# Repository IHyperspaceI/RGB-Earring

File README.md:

An earring with 10 RGB LEDs powered by a 12mm coin cell. An ATTiny1616 MCU controls the LEDs in rows, so PWM control and patterns can be made.

The tab on the bottom is to get the battery holder assembled by JLCPCB, which then will be manually desoldered and soldered to the back of the earring. The tab on the bottom can then be cut off. 

The Keystone 3000 can be ordered from other sources, however shipping is egregiously expensive from Mouser, Digikey, etc., and double sided PCBA also adds cost. Implementing a cutaway tab allows single-side PCBA and takes advantage of JLC's stock so costs associated with double-sided PCBA can be circumvented and shipping costs only need to be paid for one item.

Top Layer:

Bottom Layer

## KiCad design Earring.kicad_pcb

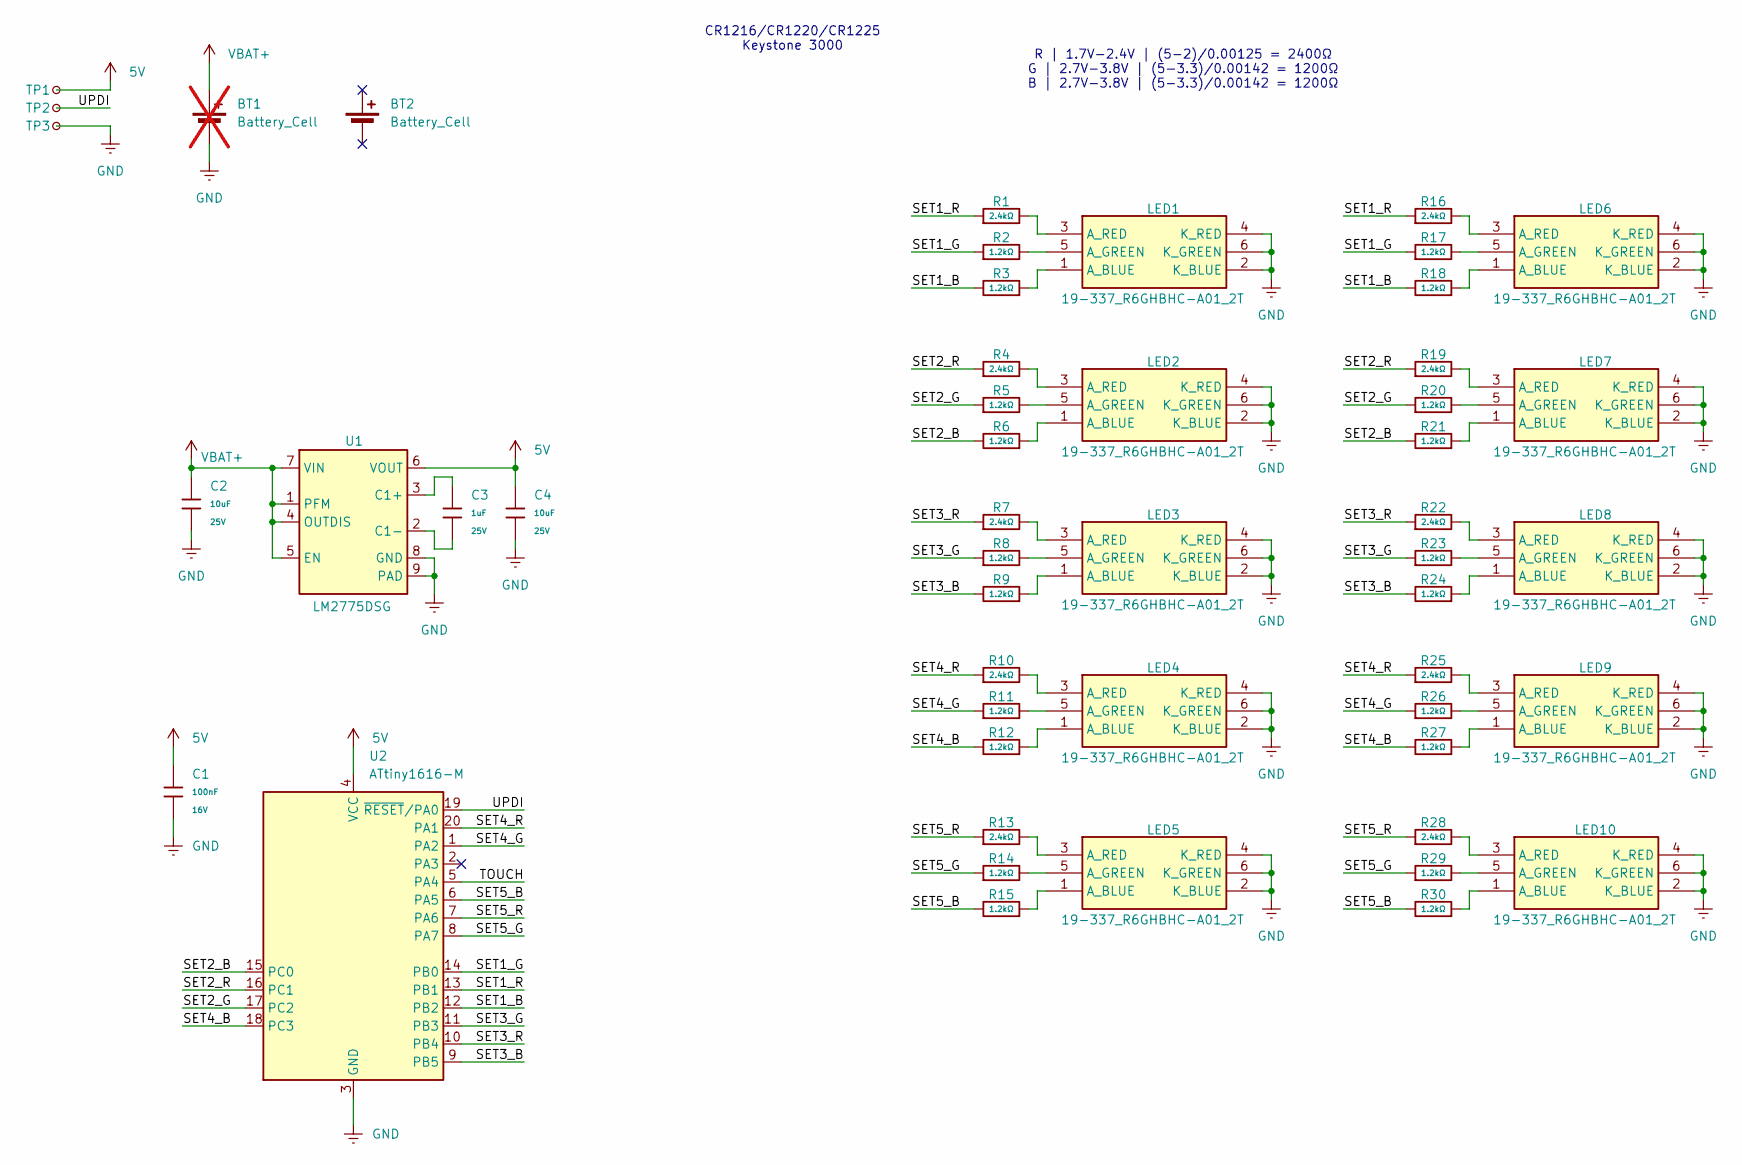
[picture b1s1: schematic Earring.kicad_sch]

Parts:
BT1: Battery_Cell; BatteryHolder_Keystone_3000_1x12mm; not fitted
BT2: Battery_Cell; BatteryHolder_Keystone_3000_1x12mm
C1: 100nF; C_0402; Voltage Rated 16V; Tolerance ±10%; Part CL05B104KO5NNNC; LCSC C1525
C2, C4: 10uF; C_0603; Voltage Rated 25V; Tolerance ±20%; Part CL10A106MA8NRNC; LCSC C96446
C3: 1uF; C_0402; Voltage Rated 25V; Tolerance ±10%; Part CL05A105KA5NQNC; LCSC C52923
LED1, LED2, LED3, LED4, LED5, LED6, LED7, LED8, LED9, LED10: 19-337_R6GHBHC-A01_2T; Mouser Part Number 638-19337R6GHBHCA01T
R1, R4, R7, R10, R13, R16, R19, R22, R25, R28: 2.4kΩ; R_0402; Overload Voltage (Max) 50V; Tolerance ±1%; Part 0402WGF2401TCE; LCSC C25882
R2, R3, R5, R6, R8, R9, R11, R12, R14, R15, R17, R18, R20, R21, R23, R24, R26, R27, R29, R30: 1.2kΩ; R_0402; Overload Voltage (Max) 50V; Tolerance ±1%; Part 0402WGF1201TCE; LCSC C25862
TP1, TP2: TestPoint_Small; TestPoint_Pad_D1.5mm
TP3: TestPoint_Small; TestPoint_Loop_D2.60mm_Drill0.9mm_Beaded
U1: LM2775DSG; WSON-8-1EP_2x2mm_P0.5mm_EP0.9x1.6mm_ThermalVias
U2: ATtiny1616-M; VQFN-20-1EP_3x3mm_P0.4mm_EP1.7x1.7mm

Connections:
5V: C1.1, C4.1, TP1.1 (1_1), U1.6 (VOUT), U2.4 (VCC)
/SET1_B: R3.2, R18.2, U2.12 (PB2)
/SET1_G: R2.1, R17.1, U2.14 (PB0)
/SET1_R: R1.1, R16.1, U2.13 (PB1)
/SET2_B: R6.2, R21.2, U2.15 (PC0)
/SET2_G: R5.1, R20.1, U2.17 (PC2)
/SET2_R: R4.1, R19.1, U2.16 (PC1)
/SET3_B: R9.2, R24.2, U2.9 (PB5)
/SET3_G: R8.1, R23.1, U2.11 (PB3)
/SET3_R: R7.1, R22.1, U2.10 (PB4)
/SET4_B: R12.2, R27.2, U2.18 (PC3)
/SET4_G: R11.1, R26.1, U2.1 (PA2)
/SET4_R: R10.1, R25.1, U2.20 (PA1)
/SET5_B: R15.2, R30.2, U2.6 (PA5)
/SET5_G: R14.1, R29.1, U2.8 (PA7)
/SET5_R: R13.1, R28.1, U2.7 (PA6)
/TOUCH: U2.5 (PA4)
/UPDI: TP2.1 (1_1), U2.19 (~RESET/PA0)
GND: BT1.2 (-), C1.2, C2.2, C4.2, LED1.2 (K_BLUE), LED1.4 (K_RED), LED1.6 (K_GREEN), LED2.2 (K_BLUE), LED2.4 (K_RED), LED2.6 (K_GREEN), LED3.2 (K_BLUE), LED3.4 (K_RED), LED3.6 (K_GREEN), LED4.2 (K_BLUE), LED4.4 (K_RED), LED4.6 (K_GREEN), LED5.2 (K_BLUE), LED5.4 (K_RED), LED5.6 (K_GREEN), LED6.2 (K_BLUE), LED6.4 (K_RED), LED6.6 (K_GREEN), LED7.2 (K_BLUE), LED7.4 (K_RED), LED7.6 (K_GREEN), LED8.2 (K_BLUE), LED8.4 (K_RED), LED8.6 (K_GREEN), LED9.2 (K_BLUE), LED9.4 (K_RED), LED9.6 (K_GREEN), LED10.2 (K_BLUE), LED10.4 (K_RED), LED10.6 (K_GREEN), TP3.1 (1_1), U1.8 (GND), U1.9 (PAD), U2.3 (GND), U2.21 (GND)
unnamed: LED1.1 (A_BLUE), R3.1
unnamed: LED1.5 (A_GREEN), R2.2
unnamed: LED1.3 (A_RED), R1.2
unnamed: LED2.1 (A_BLUE), R6.1
unnamed: LED2.5 (A_GREEN), R5.2
unnamed: LED2.3 (A_RED), R4.2
unnamed: LED3.1 (A_BLUE), R9.1
unnamed: LED3.5 (A_GREEN), R8.2
unnamed: LED3.3 (A_RED), R7.2
unnamed: LED4.1 (A_BLUE), R12.1
unnamed: LED4.5 (A_GREEN), R11.2
unnamed: LED4.3 (A_RED), R10.2
unnamed: LED5.1 (A_BLUE), R15.1
unnamed: LED5.5 (A_GREEN), R14.2
unnamed: LED5.3 (A_RED), R13.2
unnamed: LED6.1 (A_BLUE), R18.1
unnamed: LED6.5 (A_GREEN), R17.2
unnamed: LED6.3 (A_RED), R16.2
unnamed: LED7.1 (A_BLUE), R21.1
unnamed: LED7.5 (A_GREEN), R20.2
unnamed: LED7.3 (A_RED), R19.2
unnamed: LED8.1 (A_BLUE), R24.1
unnamed: LED8.5 (A_GREEN), R23.2
unnamed: LED8.3 (A_RED), R22.2
unnamed: LED9.1 (A_BLUE), R27.1
unnamed: LED9.5 (A_GREEN), R26.2
unnamed: LED9.3 (A_RED), R25.2
unnamed: LED10.1 (A_BLUE), R30.1
unnamed: LED10.5 (A_GREEN), R29.2
unnamed: LED10.3 (A_RED), R28.2
unnamed: C3.1, U1.3 (C1+)
unnamed: C3.2, U1.2 (C1-)
VBAT+: BT1.1 (+), C2.1, U1.1 (PFM), U1.4 (OUTDIS), U1.5 (EN), U1.7 (VIN)

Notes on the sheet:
R | 1.7V-2.4V | (5-2)/0.00125 = 2400Ω G | 2.7V-3.8V | (5-3.3)/0.00142 = 1200Ω B | 2.7V-3.8V | (5-3.3)/0.00142 = 1200Ω
CR1216/CR1220/CR1225 Keystone 3000

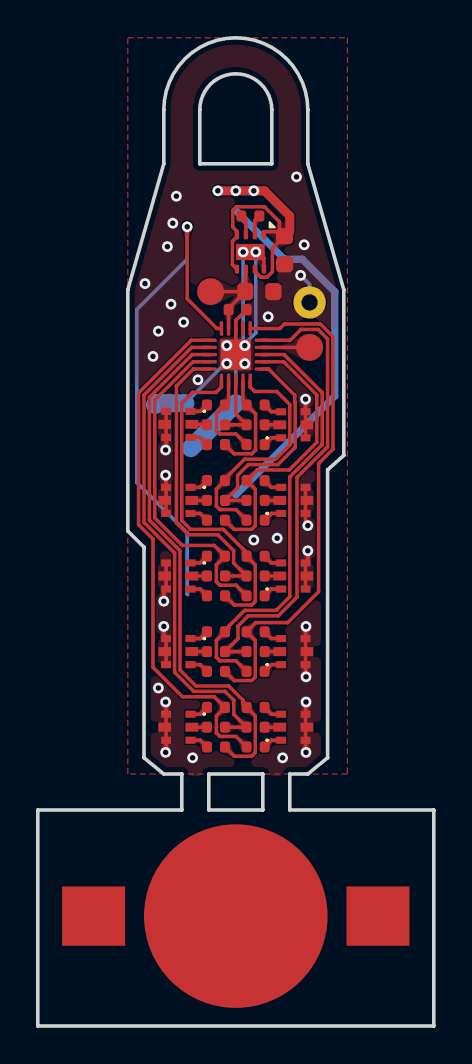
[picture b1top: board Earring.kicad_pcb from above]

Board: 2 copper layers, 22.0 x 54.9 mm, 51 parts (1 on the bottom side), 51 nets.
